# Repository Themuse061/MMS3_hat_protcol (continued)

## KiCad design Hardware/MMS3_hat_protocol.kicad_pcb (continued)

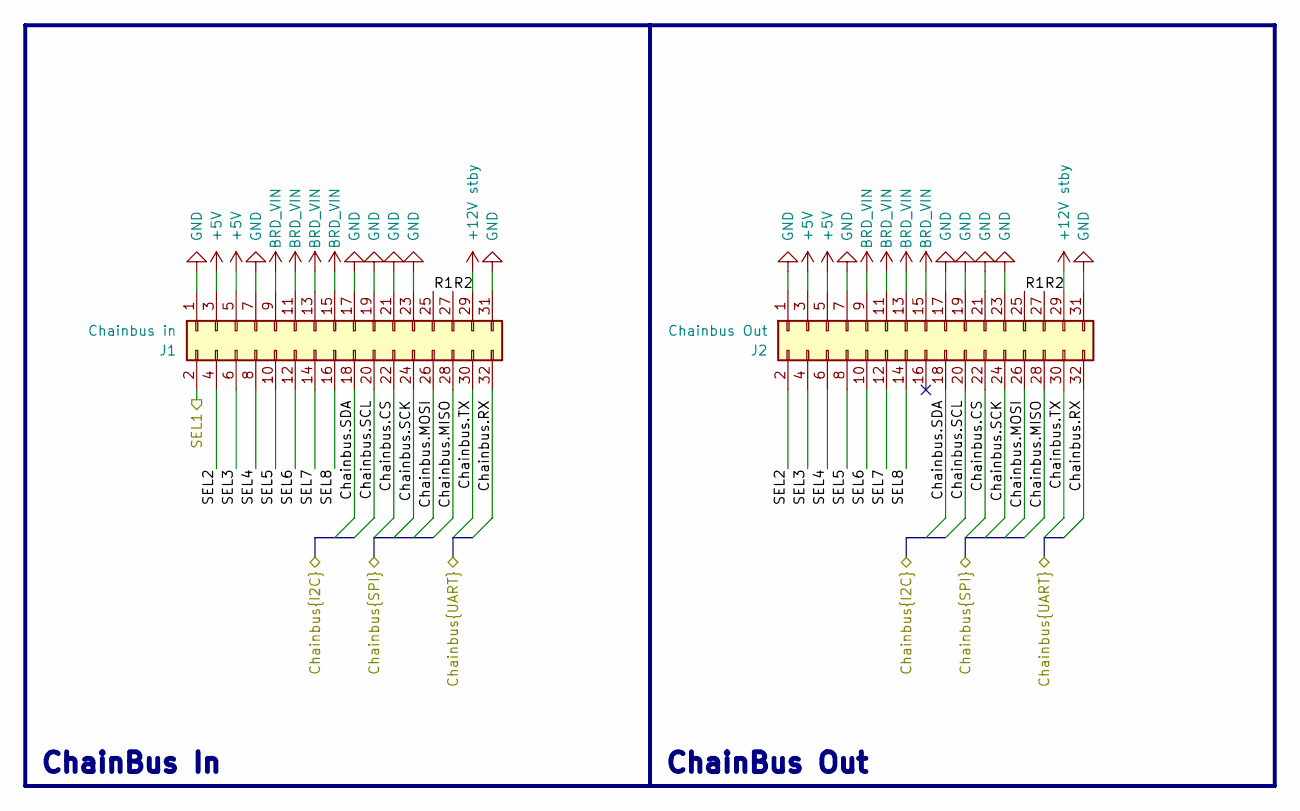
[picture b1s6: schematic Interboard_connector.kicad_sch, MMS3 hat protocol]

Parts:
J1: Chainbus in; PinHeader_2x16_P2.54mm_Vertical_SMD
J2: Chainbus Out; PinSocket_2x16_P2.54mm_Vertical_SMD

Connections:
+5V: J1.3, J1.5, J2.3, J2.5; also elsewhere on the board
+12V stby: J1.29, J2.29
/Bus_switch/Chainbus_In.CS: J1.22, J2.22; also elsewhere on the board
/Bus_switch/Chainbus_In.MISO: J1.28, J2.28; also elsewhere on the board
/Bus_switch/Chainbus_In.MOSI: J1.26, J2.26; also elsewhere on the board
/Bus_switch/Chainbus_In.RX: J1.32, J2.32; also elsewhere on the board
/Bus_switch/Chainbus_In.SCK: J1.24, J2.24; also elsewhere on the board
/Bus_switch/Chainbus_In.SCL: J1.20, J2.20; also elsewhere on the board
/Bus_switch/Chainbus_In.SDA: J1.18, J2.18; also elsewhere on the board
/Bus_switch/Chainbus_In.TX: J1.30, J2.30; also elsewhere on the board
/Bus_switch/SEL1: J1.2; also elsewhere on the board
/Interboard_connector/R1: J1.25, J2.25
/Interboard_connector/R2: J1.27, J2.27
/Interboard_connector/SEL2: J1.4, J2.2
/Interboard_connector/SEL3: J1.6, J2.4
/Interboard_connector/SEL4: J1.8, J2.6
/Interboard_connector/SEL5: J1.10, J2.8
/Interboard_connector/SEL6: J1.12, J2.10
/Interboard_connector/SEL7: J1.14, J2.12
/Interboard_connector/SEL8: J1.16, J2.14
BRD_VIN: J1.9, J1.11, J1.13, J1.15, J2.9, J2.11, J2.13, J2.15
GND: J1.1, J1.7, J1.17, J1.19, J1.21, J1.23, J1.31, J2.1, J2.7, J2.17, J2.19, J2.21, J2.23, J2.31; also elsewhere on the board

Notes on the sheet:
ChainBus In
ChainBus Out

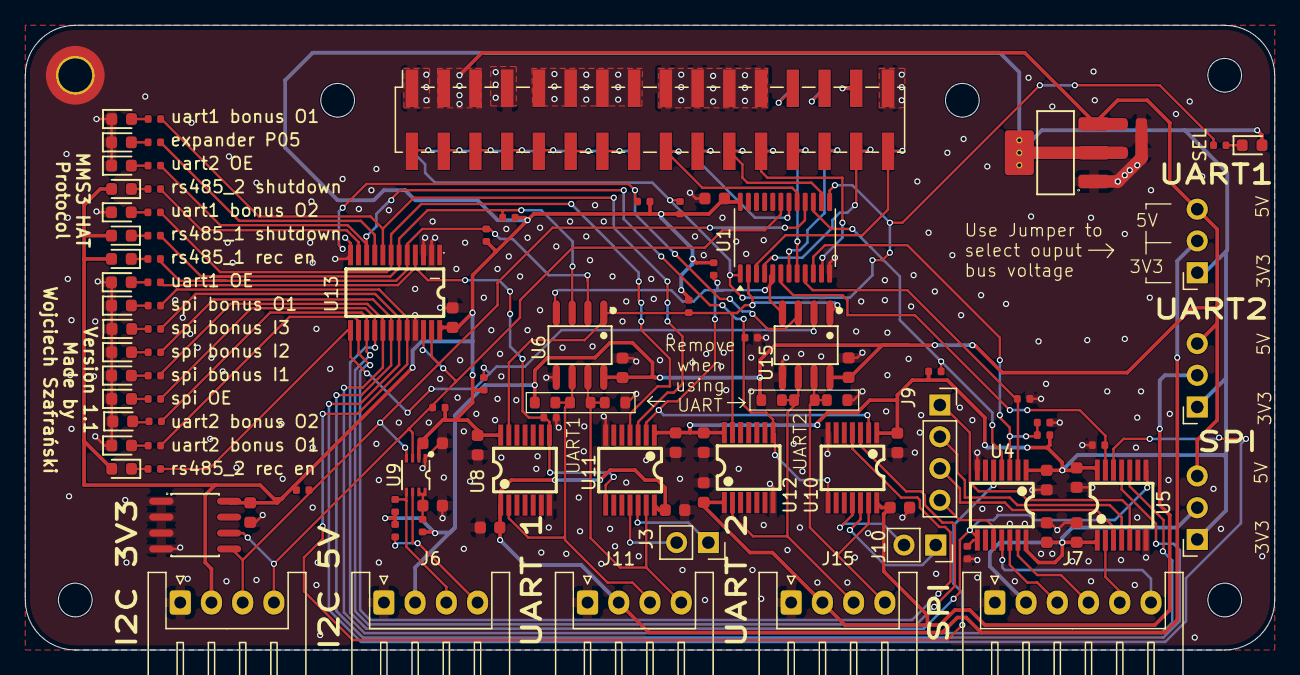
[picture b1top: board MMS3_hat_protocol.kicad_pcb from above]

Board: 2 copper layers, 100.0 x 50.0 mm, 113 parts (1 on the bottom side), 86 nets.

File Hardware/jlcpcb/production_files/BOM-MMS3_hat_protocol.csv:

Comment,Designator,Footprint,LCSC,Quantity
100nF,"C1,C10,C11,C12,C13,C14,C15,C17,C18,C19,C2,C20,C21,C22,C4,C6,C7,C8,C9",C_0603,C14663,19
10kΩ,"R10,R11,R15,R16,R17,R18,R19,R2,R20,R22,R3,R38,R40,R42,R44,R6,R8,R9",R_0402,C25744,18
10uF,"C3,C5",C_0603,C19702,2
120Ω,"R25,R28",R_0603,C22787,2
200kΩ,R7,R_0402,C25764,1
330Ω,"R12,R13,R14,R21,R37,R39,R41,R43,R45,R46,R47,R48,R49,R5,R50,R51,R52",R_0402,C25104,17
510Ω,"R23,R24,R26,R27",R_0603,C23193,4
AMS1117,U3,SOT-223-3_L6.5-W3.4-P2.30-LS7.0-BR,C6186,1
M24C64,U2,SOIC-8_L5.0-W4.0-P1.27-LS6.0-BL,C79988,1
MAX13487EESA,"U15,U6",SOIC-8_L4.9-W3.9-P1.27-LS6.0-BL,C18347,2
PCA9306DCUR,U9,SSOP-8_L2.0-W2.3-P0.50-LS3.1-BR,C33196,1
Red,"D10,D15,D16,D17,D18,D19,D20,D21,D22,D23,D24,D25,D26,D6,D7,D8,D9",D_0603,C2286,17
SN74CB3Q3384APW,U1,TSSOP-24_4.4x7.8mm_P0.65mm,C469874,1
TCA9535PWR_C130204,U13,TSSOP-24_L7.8-W4.4-P0.65-LS6.4-BL,C130204,1
TXU0104PWR,"U10,U11,U12,U4,U5,U8",TSSOP-14_L5.0-W4.4-P0.65-LS6.4-BL,C2938871,6
Conn_01x02_Pin,J10,PinSocket_1x02_P2.54mm_Vertical,,1
Conn_01x04_Pin,J9,PinSocket_1x04_P2.54mm_Vertical,,1
Chainbus Out,J2,PinSocket_2x16_P2.54mm_Vertical_SMD,,1
Conn_01x03_Pin,J5,PinSocket_1x03_P2.54mm_Horizontal,,1
Conn_01x02_Pin,J3,PinSocket_1x02_P2.54mm_Vertical,,1
Conn_01x04_Pin,J15,JST_XH_S4B-XH-A_1x04_P2.50mm_Horizontal,,1
Conn_01x03_Pin,J14,PinSocket_1x03_P2.54mm_Horizontal,,1
Conn_01x04_Pin,J11,JST_XH_S4B-XH-A_1x04_P2.50mm_Horizontal,,1
Conn_01x03_Pin,J8,PinSocket_1x03_P2.54mm_Horizontal,,1
Conn_01x04_Pin,J4,JST_XH_S4B-XH-A_1x04_P2.50mm_Horizontal,,1
Conn_01x06_Pin,J7,JST_XH_S6B-XH-A_1x06_P2.50mm_Horizontal,,1
Conn_01x04_Pin,J6,JST_XH_S4B-XH-A_1x04_P2.50mm_Horizontal,,1
Chainbus in,J1,PinHeader_2x16_P2.54mm_Vertical_SMD,,1

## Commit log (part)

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2026-03-05 some schematic done
2026-04-18 finished schematic
2026-04-20 generated final bom
2026-06-09 added documentation
